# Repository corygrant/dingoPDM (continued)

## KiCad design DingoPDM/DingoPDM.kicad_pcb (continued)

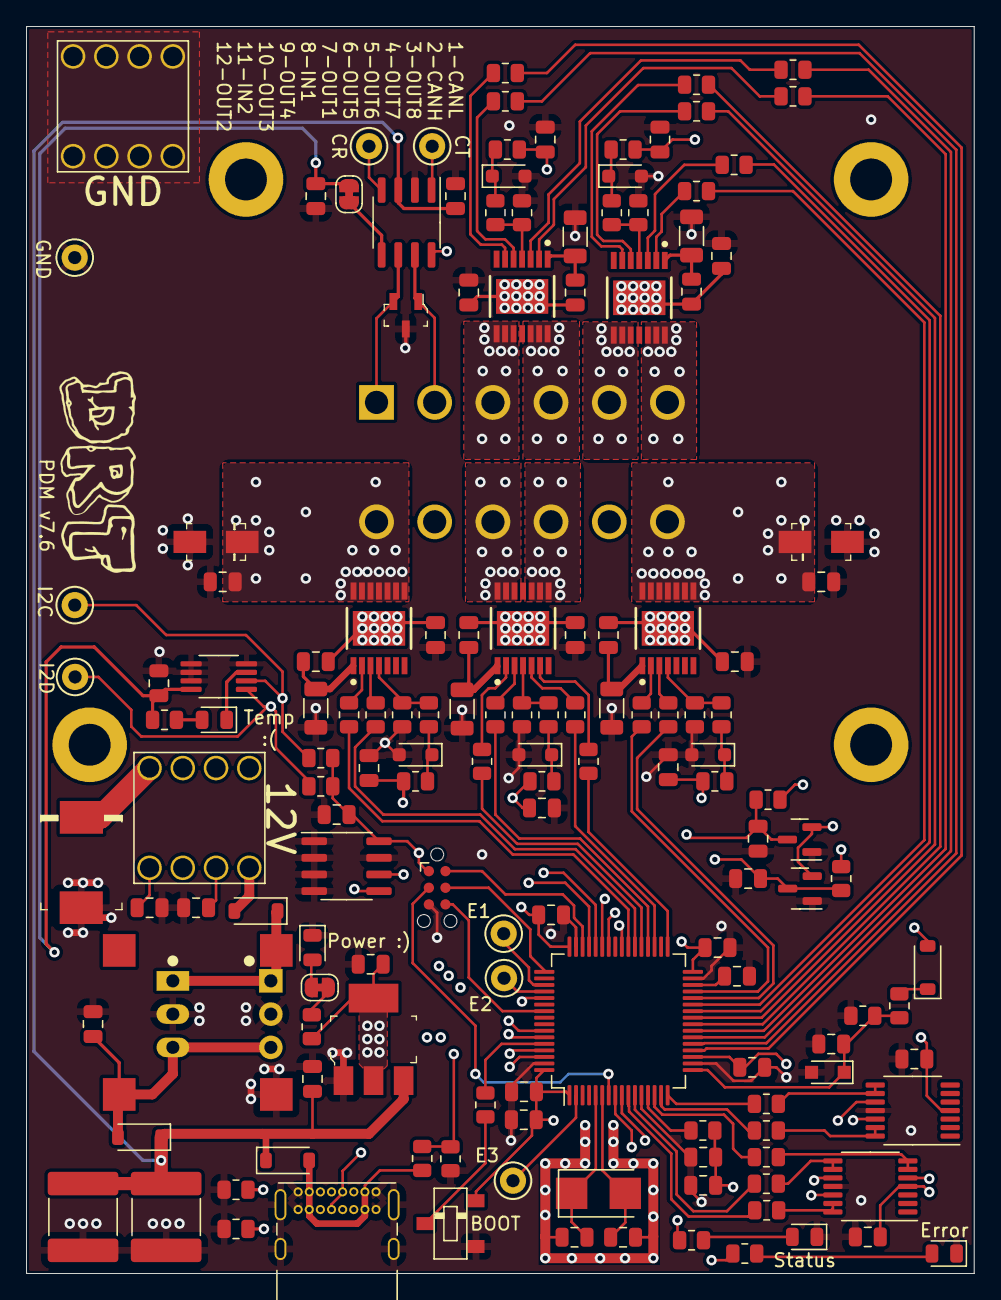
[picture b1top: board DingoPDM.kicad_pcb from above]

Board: 4 copper layers, 72.4 x 95.2 mm, 158 parts (1 on the bottom side), 117 nets.

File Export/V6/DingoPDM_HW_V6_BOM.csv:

"Reference","Value","Footprint","Digi-Key_PN","LCSC","Qty"
"C1","100nF","Capacitor_SMD:C_0805_2012Metric","478-1395-1-ND","C49678","1"
"C2","100nF","Capacitor_SMD:C_0805_2012Metric","478-1395-1-ND","C49678","1"
"C3","10uF","Capacitor_SMD:C_0805_2012Metric","445-11516-1-ND","C15850","1"
"C4","22uF","Capacitor_SMD:C_0805_2012Metric","490-10749-1-ND","C45783","1"
"C5","100nF","Capacitor_SMD:C_0805_2012Metric","478-1395-1-ND","C49678","1"
"C6","10uF","Capacitor_SMD:C_0805_2012Metric","445-11516-1-ND","C15850","1"
"C7","27pF","Capacitor_SMD:C_0805_2012Metric","478-10518-1-ND","C1808","1"
"C8","27pF","Capacitor_SMD:C_0805_2012Metric","478-10518-1-ND","C1808","1"
"C9","100nF","Capacitor_SMD:C_0805_2012Metric","478-1395-1-ND","C49678","1"
"C11","100nF","Capacitor_SMD:C_0805_2012Metric","478-1395-1-ND","C49678","1"
"C12","100nF","Capacitor_SMD:C_0805_2012Metric","478-1395-1-ND","C49678","1"
"C13","100nF","Capacitor_SMD:C_0805_2012Metric","478-1395-1-ND","C49678","1"
"C14","4.7uF","Capacitor_SMD:C_0805_2012Metric","1276-2873-1-ND","C1779","1"
"C15","10nF","Capacitor_SMD:C_0805_2012Metric","311-1136-1-ND","C1710","1"
"C16","1uF","Capacitor_SMD:C_0805_2012Metric","311-1365-1-ND","C28323","1"
"C17","100nF","Capacitor_SMD:C_0805_2012Metric","478-1395-1-ND","C49678","1"
"C18","1uF","Capacitor_SMD:C_0805_2012Metric","311-1365-1-ND","C28323","1"
"C19","10nF","Capacitor_SMD:C_0805_2012Metric","311-1136-1-ND","C1710","1"
"C20","10nF","Capacitor_SMD:C_0805_2012Metric","311-1136-1-ND","C1710","1"
"C21","100nF","Capacitor_SMD:C_0805_2012Metric","478-1395-1-ND","C49678","1"
"C22","47nF","Capacitor_SMD:C_0805_2012Metric","399-1166-1-ND","C520039","1"
"C23","100nF","Capacitor_SMD:C_0805_2012Metric","478-1395-1-ND","C49678","1"
"C24","10nF","Capacitor_SMD:C_0805_2012Metric","311-1136-1-ND","C1710","1"
"C25","220pF","Capacitor_SMD:C_0805_2012Metric","399-1138-1-ND","C576920","1"
"C26","47nF","Capacitor_SMD:C_0805_2012Metric","399-1166-1-ND","C520039","1"
"C27","100nF","Capacitor_SMD:C_0805_2012Metric","478-1395-1-ND","C49678","1"
"C28","10nF","Capacitor_SMD:C_0805_2012Metric","311-1136-1-ND","C1710","1"
"C29","220pF","Capacitor_SMD:C_0805_2012Metric","399-1138-1-ND","C576920","1"
"C30","47nF","Capacitor_SMD:C_0805_2012Metric","399-1166-1-ND","C520039","1"
"C31","100nF","Capacitor_SMD:C_0805_2012Metric","478-1395-1-ND","C49678","1"
"C32","220pF","Capacitor_SMD:C_0805_2012Metric","399-1138-1-ND","C576920","1"
"D1","3.3V","Diode_SMD:D_SOD-323_HandSoldering","1727-5150-1-ND","C177016","1"
"D2","SMCJ20CA","digikey-footprints:DO-214AB_TVS","SMCJ20CABCT-ND","C2760132","1"
"D3","GRN","LED_SMD:LED_0805_2012Metric","475-1410-1-ND","C2899888","1"
"D4","NUP2105LT1G","digikey-footprints:SOT-23-3","NUP2105LT1GOSCT-ND","C2976509","1"
"D5","RED","LED_SMD:LED_0805_2012Metric","475-1278-1-ND","C2899997","1"
"D6","BAT54S","Package_TO_SOT_SMD:SOT-23","BAT54SLT1GOSCT-ND","C47546","1"
"D7","BAT54S","Package_TO_SOT_SMD:SOT-23","BAT54SLT1GOSCT-ND","C47546","1"
"D8","BYG23M","digikey-footprints:DO-214AC","BYG23M-E3/TR3GICT-ND","C141573","1"
"D9","3.3V","Diode_SMD:D_SOD-323_HandSoldering","1727-5150-1-ND","C177016","1"
"D10","BYG23M","digikey-footprints:DO-214AC","BYG23M-E3/TR3GICT-ND","C141573","1"
"D11","3.3V","Diode_SMD:D_SOD-323_HandSoldering","1727-5150-1-ND","C177016","1"
"D12","3.3V","Diode_SMD:D_SOD-323_HandSoldering","1727-5150-1-ND","C177016","1"
"FB1","Ferrite_Bead_Small","Resistor_SMD:R_0805_2012Metric","490-1054-1-ND","C85840","1"
"J1","RedCubeTerminal","RedCube:M6_Hole_8Pin_7461084","732-3203-ND",,"1"
"J2","RedCubeTerminal","RedCube:M6_Hole_8Pin_7461084","732-3203-ND",,"1"
"J3","Conn_01x12","Deutsch_DT:DT15-12PA","1734-1027-ND",,"1"
"R1","47k","Resistor_SMD:R_0805_2012Metric","311-47.0KCRCT-ND","C327035","1"
"R2","10k","Resistor_SMD:R_0805_2012Metric","311-10.0KCRDKR-ND","C17414","1"
"R3","120R","Resistor_SMD:R_0805_2012Metric","311-120CRCT-ND","C229076","1"
"R4","10k","Resistor_SMD:R_0805_2012Metric","311-10.0KCRDKR-ND","C17414","1"
"R5","1k","Resistor_SMD:R_0805_2012Metric","311-1.0KARCT-ND","C17513","1"
"R6","10k","Resistor_SMD:R_0805_2012Metric","311-10.0KCRDKR-ND","C17414","1"
"R7","10k","Resistor_SMD:R_0805_2012Metric","311-10.0KCRDKR-ND","C17414","1"
"R8","120R","Resistor_SMD:R_0805_2012Metric","311-120CRCT-ND","C229076","1"
"R9","4.7k","Resistor_SMD:R_0805_2012Metric","311-4.70KCRCT-ND","C17673","1"
"R10","4.7k","Resistor_SMD:R_0805_2012Metric","311-4.70KCRCT-ND","C17673","1"
"R11","1.2k","Resistor_SMD:R_0805_2012Metric","311-1.20KCRCT-ND","C727987","1"
"R12","1.2k","Resistor_SMD:R_0805_2012Metric","311-1.20KCRCT-ND","C727987","1"
"R13","4.7k","Resistor_SMD:R_0805_2012Metric","311-4.70KCRCT-ND","C17673","1"
"R14","4.7k","Resistor_SMD:R_0805_2012Metric","311-4.70KCRCT-ND","C17673","1"
"R15","1.2k","Resistor_SMD:R_0805_2012Metric","311-1.20KCRCT-ND","C727987","1"
"R16","47R 1/4W","Resistor_SMD:R_1206_3216Metric","311-47.0FRCT-ND","C2907508","1"
"R17","4.7k","Resistor_SMD:R_0805_2012Metric","311-4.70KCRCT-ND","C17673","1"
"R18","4.7k","Resistor_SMD:R_0805_2012Metric","311-4.70KCRCT-ND","C17673","1"
"R19","4.7k","Resistor_SMD:R_0805_2012Metric","311-4.70KCRCT-ND","C17673","1"
"R20","4.7k","Resistor_SMD:R_0805_2012Metric","311-4.70KCRCT-ND","C17673","1"
"R21","1.2k","Resistor_SMD:R_0805_2012Metric","311-1.20KCRCT-ND","C727987","1"
"R22","47R 1/4W","Resistor_SMD:R_1206_3216Metric","311-47.0FRCT-ND","C2907508","1"
"R23","4.7k","Resistor_SMD:R_0805_2012Metric","311-4.70KCRCT-ND","C17673","1"
"R24","4.7k","Resistor_SMD:R_0805_2012Metric","311-4.70KCRCT-ND","C17673","1"
"R25","1.2k","Resistor_SMD:R_0805_2012Metric","311-1.20KCRCT-ND","C727987","1"
"R26","4.7k","Resistor_SMD:R_0805_2012Metric","311-4.70KCRCT-ND","C17673","1"
"R27","4.7k","Resistor_SMD:R_0805_2012Metric","311-4.70KCRCT-ND","C17673","1"
"R28","4.7k","Resistor_SMD:R_0805_2012Metric","311-4.70KCRCT-ND","C17673","1"
"R29","4.7k","Resistor_SMD:R_0805_2012Metric","311-4.70KCRCT-ND","C17673","1"
"R30","1.2k","Resistor_SMD:R_0805_2012Metric","311-1.20KCRCT-ND","C727987","1"
"R31","47R 1/4W","Resistor_SMD:R_1206_3216Metric","311-47.0FRCT-ND","C2907508","1"
"R32","4.7k","Resistor_SMD:R_0805_2012Metric","311-4.70KCRCT-ND","C17673","1"
"R33","4.7k","Resistor_SMD:R_0805_2012Metric","311-4.70KCRCT-ND","C17673","1"
"R34","4.7k","Resistor_SMD:R_0805_2012Metric","311-4.70KCRCT-ND","C17673","1"
"R35","4.7k","Resistor_SMD:R_0805_2012Metric","311-4.70KCRCT-ND","C17673","1"
"R36","4.7k","Resistor_SMD:R_0805_2012Metric","311-4.70KCRCT-ND","C17673","1"
"R37","4.7k","Resistor_SMD:R_0805_2012Metric","311-4.70KCRCT-ND","C17673","1"
"U1","VXO780x-500-M","CUI_Regulators:VXO78x-500-M","102-VXO7805-500-M-CT-ND",,"1"
"U2","LD1117S33CTR","digikey-footprints:SOT-223","497-1241-1-ND","C35879","1"
"U3","PCA82C250","Package_SO:SOIC-8_3.9x4.9mm_P1.27mm","568-10316-1-ND","C7439","1"
"U4","STM32F303CCTx","Package_QFP:LQFP-48_7x7mm_P0.5mm","497-13318-ND","C81523","1"
"U5","MB85RC256V","Package_SO:SOIC-8_3.9x4.9mm_P1.27mm","865-1261-1-ND","C47538","1"
"U6","MCP9808","Package_SO:MSOP-8_3x3mm_P0.65mm","MCP9808T-E/MSCT-ND","C129490","1"
"U7","LM324","Package_SO:TSSOP-14_4.4x5mm_P0.65mm","497-7330-1-ND","C7944","1"
"U8","BTS700n-1EPP","Profet:TDSO-14","BTS70021EPPXUMA1CT-ND","C534824","1"
"U9","BTS700n-1EPP","Profet:TDSO-14","BTS70021EPPXUMA1CT-ND","C534824","1"
"U11","BTS7008-2EPA","Profet:TDSO-14","BTS70082EPAXUMA1CT-ND","C2150060","1"
"U12","BTS724G","Package_SO:Infineon_PG-DSO-20-32","BTS724GXUMA1CT-ND","C82656","1"
"Y1","8mHz","Crystals_Modify:Crystal_SMD_5032-2Pin_5.0x3.2mm_HandSoldering","535-10630-1-ND","C144380","1"

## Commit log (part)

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2021-04-10 Reorganizing files
2022-06-17 V3 As Built
2022-10-15 Kicad V6 updates
2022-12-07 Swapped to AMPSEAL 14 pins
2022-12-07 Removed unused IRQs, added pd res on PF GPIO reset
2022-12-13 layout finished
2022-12-13 autosave crap
2023-01-05 Removed files from the index (now ignored)
2023-01-05 updated gitignore
2023-02-06 Moved folders
2023-02-09 Removed old notes
2023-02-09 Updated gerbers
2023-02-10 Added export, fixed some PNs
2023-02-23 V5 changes
    Changed tracks/clearances/DRC to meet JLCPCB 2oz rules. Changed on switch to 12V input. Switched to TagConnect
2023-02-24 Documentation cleanup
2023-02-24 V5 As Built
    -Changed ADS1015 to MAX11613EUA+T due to supply issues
    -Changed PCB to match JLCPCB 2oz rules
    -Changed ON_SW input to 12V switched
    -Switched to TagConnect TC2030
    -Changed pin positions of GND, IN1, IN2
2023-02-24 No black soldermask with 2oz available at JLCPCB
2023-02-26 Error on the bottom silk legend, updated step file
2023-03-11 Incorrect PN for some diodes and resistors
2023-03-11 Wrong opto-isolator part number
2023-04-02 Changed schematic sheet size to letter
2023-04-02 Added black/white and dark PDF schematics
2023-05-04 Added V5 case design
2023-07-28 Redesigned to a smaller unit
    4x high current, 2x med current, 4x low current, 2x digital inputs
2023-08-01 Added documentation, finished and cleaned design
2023-08-01 Added photos and step file, updated README
2023-08-19 Changed to STM32F446RE
2023-08-20 Routed V7
2023-08-21 Small edits
2023-08-21 Updated V7 Exports
2023-08-21 Small updates
2023-09-05 V7.1 Fixes
    SDA/SCL mixed up on FRAM, added status LEDs, switched to thermal relief zones
2023-09-12 Add diode, disconnect PB13, fix USB VBUS
2023-09-12 Fixed local machine 3D model issue
2023-09-12 Forgot to save
2023-11-25 Added mkdocs files
2023-11-26 Trying out Github pages and mkdocs material
2023-11-26 Docs additions
2023-11-26 Remove site
2023-11-26 Docs test
2023-11-26 Framing out docs
2023-11-26 More docs testing
2023-11-26 Image test
2023-11-26 Fixed doc images
2023-11-27 Adding docs
2023-11-28 Removing duplicate and old documentation
2023-11-28 Trying to fix images with relative paths
2023-11-28 Different image paths
2023-11-28 SVG use a different relative path
2023-11-28 Images still not working
2023-11-28 Another relative path
2023-11-28 Another path
2023-11-28 Another path again
2023-11-28 Path for png still not working
2023-11-28 Extra dots
2023-11-29 Delete docs/Images directory
    No idea why this directory exists, but not on my local repo
2023-11-29 Adding images back after deleting strange directory
2023-11-29 Removing README content
2023-11-29 Cleaned up the image edges
2023-11-29 New PCB image and cleaning up mkdocs
2023-12-01 Status and Error LED part num switched
2023-12-01 Remove lck files
2023-12-07 Incorrect screw length
2024-02-04 Updated case design
    Added light pipes, label and fixed height due to thermal pad material
2024-02-05 Mounting holes and bad image
2024-02-05 Text wasn't very readable, fixed fill
2024-02-05 Changed to lowercase
2024-02-05 Lowercase issues
2024-03-21 Updated JLC zener diode part and batt volt divider
    The previous zener diode had too low of a breakdown zener voltage.
    The previous voltage divider was also too high of an output voltage, swapped R2 to lower the max voltage to well below the breakdown zener voltage
2024-03-25 Update JLC part numbers for in stock ones
2024-03-25 Deployed 6bb3373 with MkDocs version: 1.5.3
2024-04-09 Firmware updating docs added
2024-04-10 doc images and more sections added
2024-04-10 Update ci.yml
    added mkdocs-glightbox
2024-04-12 Add WiperModule info to docs
2024-04-24 Fixed error in case model
    #8
2024-05-01 Updated photos
2024-05-05 Updated docs links
2024-05-08 Fixed missing silkscreen values
    BOOT, E1, E2, E3 labels were missing
2024-05-10 Fixed Case.step
    Previous model was the whole assembly
2024-05-21 Update mkdocs.yml
    Re-enabled search
2024-05-27 Fixed USB, power LED and CAN standby
    And increased screw hole size
    #9, #11, #12, #13
2024-05-29 Adding firmware CAN docs
2024-05-30 CAN Output info added
2024-05-31 Adding more CAN docs
2024-06-04 Updated docs
2024-06-11 Updated images
2024-06-13 CAN and var map docs
2024-06-17 Message info added to docs
2024-06-17 LED and error information added
2024-06-18 Updated toolbar docs
2024-06-22 docs, fixed message numbers
2024-07-01 docs updated flasher and varmap
2024-07-01 Deployed c4189dd with MkDocs version: 1.6.0
2024-07-13 Update gitignore
2024-07-13 gitignore
2024-07-13 Deployed 9b18875 with MkDocs version: 1.6.0
2024-08-24 Docs update
2024-08-31 FwUpdate docs update
2024-09-03 Added diode for reverse battery protection
    #14
2024-09-03 Update docs
2024-09-06 Updated to Kicad 8
2024-09-07 dingoPDM-Max info added
2024-09-07 More dingoPDM-Maxx update
2024-09-07 Deployed b5b9a05 with MkDocs version: 1.6.1
2024-12-31 add dimensions drawing
2024-12-31 add wiring aid stl model
2025-01-24 updated wiring aid stl
2025-01-29 Deployed 3ad8763 with MkDocs version: 1.6.1
2025-02-22 add wavedrom bitfield build svgs
2025-02-26 add more bitfields
2025-02-26 Deployed 20f7656 with MkDocs version: 1.6.1
2025-03-02 update can TX docs
2025-03-02 can and can input msg doc update
2025-03-02 Deployed 3eb4ed5 with MkDocs version: 1.6.1
2025-03-04 docs, complete settings can msgs
2025-03-04 docs, add always sent to can tx table
2025-03-04 docs, update always sent emoji
2025-03-04 docs, update can input
2025-03-04 docs, fix can input
2025-03-04 docs, update var map
2025-03-04 docs, xychart test
2025-03-04 docs, update step links
2025-03-05 docs, add mkdocs charts
2025-03-05 docs, double markdown_extensions
2025-03-05 docs, fix mkdocs.yml again
2025-03-08 docs - moved stress tests to thermal
2025-03-08 Deployed 944bbcc with MkDocs version: 1.6.1
2025-03-10 add pwm thermal tests
2025-03-10 Deployed fffc774 with MkDocs version: 1.6.1
2025-03-11 docs - more thermal tests
2025-03-12 docs - thermal degrees f to c
2025-03-12 docs - thermal graph add tool tip
2025-03-12 docs - fix thermal tooltip
2025-03-12 docs - changing thermal chart type
2025-03-13 docs - add interactive to thermal chart
2025-03-13 docs - update getting started intro
2025-03-13 docs - small changes
2025-03-14 docs - update can settings msg
2025-03-14 Deployed 3560a98 with MkDocs version: 1.6.1
2025-03-16 docs - add maps
2025-03-16 docs - auto reload charts
2025-03-17 docs - add fb link
2025-03-17 Deployed d4025a4 with MkDocs version: 1.6.1
2025-03-24 add shields to readme
2025-03-25 update shields
2025-03-25 update shields again
2025-03-25 dbc files and dbc builder added
2025-03-25 docs - add shields
2025-03-25 Deployed 22c08a1 with MkDocs version: 1.6.1
2025-04-17 docs - add to firmware
2025-04-17 undo accidental changes to kicad
2025-04-17 started adding test points
2025-04-17 Deployed 0325101 with MkDocs version: 1.6.1
2025-04-24 run docs workflow only on docs change
2025-04-24 move dbc to fw repo
2025-04-24 docs - add dbc link
2025-04-30 docs - add to maps
2025-04-30 docs - can't forget the flag
2025-04-30 docs - add wiring example
2025-04-30 docs - fix diagram background
2025-04-30 Deployed 432e1c7 with MkDocs version: 1.6.1
2025-05-07 add DC-DC converter options
2025-05-13 docs - adding keypad can settings
2025-05-21 docs - add dials
2025-05-21 docs - keypad msgs
2025-05-23 docs - fix dial message
2025-06-08 docs - remove has dial
2025-06-17 add 5v cap
2025-06-17 add v7.5 exports
2025-06-17 add dark schematic
2025-06-17 docs - keypad
2025-06-17 Deployed e865864 with MkDocs version: 1.6.1
2025-06-17 switch to ceramic caps
2025-06-17 updated silk version
2025-07-07 update part nums, remove custom drc, add max thermal
2025-07-07 Deployed e23b1eb with MkDocs version: 1.6.1
2025-08-19 move footprints to project library
2025-09-30 docs - add iboms
2025-09-30 PCB Checklist added.
2025-09-30 docs - update pwm can msg
2025-10-01 docs - update maps
2025-10-01 docs - add flags of course
2025-10-01 docs - update states
2025-10-01 Deployed 555b511 with MkDocs version: 1.6.1
2025-12-10 docs - add build info
2025-12-10 Deployed feb6405 with MkDocs version: 1.6.1
2026-01-05 add note about dingoConfig
2026-01-13 docs - add empty custom, update fw intro page
2026-01-13 Deployed b3d5da5 with MkDocs version: 1.6.1
2026-01-13 update gh pages deployment
2026-01-23 add custom.md, thanks jabbarider
2026-01-23 adding documentation status table
2026-01-24 docs - add radlok info
2026-01-24 docs - add den pin
2026-03-21 remove old kicad files
2026-03-27 update can transceiver, add diode to batt sense
2026-03-27 undo previous
2026-03-27 make v7.6 changes, update can transceiver
2026-03-30 fix 3.3v plane that disappeared
2026-06-20 add paleppp case design
